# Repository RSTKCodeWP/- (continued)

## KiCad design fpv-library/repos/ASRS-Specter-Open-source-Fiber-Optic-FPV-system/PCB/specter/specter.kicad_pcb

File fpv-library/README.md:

# FPV Library

Automated mirror and catalog of FPV / drone open-source projects from GitHub.

## Is continuous sync realistic?

**Yes, with limits.**

| What works well | What needs care |
|-----------------|-----------------|
| Daily `discover` + `sync` via GitHub Actions | GitHub API rate limits (~5k req/hr authenticated) |
| Tracking upstream commit SHA per repo | Large repos (ardupilot, betaflight, firmware) take longer to clone — still synced |
| Owner expansion (other repos by same author) | Not every search hit is worth mirroring — scoring filters noise |
| Auto-commit when upstream changes | Licenses must be respected (GPL, etc.) |

This library keeps a **`catalog.json`** manifest: source repo, local path, last upstream commit, discovery method, relevance score.

## Layout

```
fpv-library/
  catalog.json          # manifest of all tracked projects
  STRUCTURE.md          # what each folder/file means (UA + EN)
  repos/                # auto-synced mirrors (discovered repos)
  ../OpenIPC/           # example: full git copies of a GitHub org
  manifests/            # release SHA256 manifests (Caddx firmware, ground config)
  ground-config/        # downloaded Caddx Ground Configuration binaries (gitignored)
  scripts/
    discover.py         # parse GitHub search + expand owners
    discover_themes.py  # multi-query themed discovery (GCS, fiber, WFB, …)
    sync.py             # full git mirror: clone, fetch, LFS, submodules
    discover_org.py     # register all repos from a GitHub org (e.g. OpenIPC)
    generate_repo_index.py  # write ../REPOS.md (full project list)
    register_legacy.py  # register hand-copied example folders at repo root
  THEMED.md             # curated highlights by category
  HOOKS.md              # auto-generated interesting / watch list
```

**Full project index (description, path, date, size):** [`../REPOS.md`](../REPOS.md)  
**Exhibition wiki (one card per folder on disk):** [`../wiki/Home.md`](../wiki/Home.md)  
**Daily mirror policy:** [`MIRROR.md`](MIRROR.md) · [`../docs/MIRROR_POLICY.md`](../docs/MIRROR_POLICY.md)  
**Repository layout:** [`../docs/STRUCTURE.md`](../docs/STRUCTURE.md) · [`STRUCTURE.md`](STRUCTURE.md)

## Usage

### Discover (GitHub search + owner crawl)

```bash
# Page 4 of Fpv search, expand each owner's other repos
python3 fpv-library/scripts/discover.py \
  --search Fpv \
  --page 4 \
  --min-score 2.0 \
  --expand-owners \
  --owner-limit 5

# Pages 1–5
python3 fpv-library/scripts/discover.py --search Fpv --pages 1-5 --expand-owners

# Themed batch: GCS, fiber, WFB, OpenIPC, DroneBridge, owner ecosystems
python3 fpv-library/scripts/discover_themes.py --pages 1-2 --min-score 2.5

# Full org library (e.g. all OpenIPC repos → OpenIPC/<repo>/)
python3 fpv-library/scripts/discover_org.py --org OpenIPC --verdict keep
python3 fpv-library/scripts/sync.py --owner OpenIPC --verdict keep
```

See [`THEMED.md`](THEMED.md) for curated project highlights.

### Daily mirror (update + backfill)

```bash
# Full daily cycle (same as CI)
python3 fpv-library/scripts/sync_daily.py

# Or manually:
python3 fpv-library/scripts/sync.py --all --verdict keep --update-only
python3 fpv-library/scripts/sync.py --all --verdict keep --new-only --max-per-run 25
```

### Sync upstream updates

```bash
python3 fpv-library/scripts/sync.py --all
python3 fpv-library/scripts/sync.py --source RotorHazard/RotorHazard
```

Each synced folder gets `.fpv-library.json` with upstream commit metadata.

### Register legacy examples

```bash
python3 fpv-library/scripts/register_legacy.py
```

## Automation

`.github/workflows/fpv-library-sync.yml` runs **daily** (06:00 UTC):

1. **Keyword discovery** — rotating batch from `keywords.txt`
2. **Themed discovery** — GCS / link / fiber queries + owner ecosystems
3. **Triage** — `keep` / `watch` / `skip`; write `HOOKS.md`
4. **Register** — root-level project folders → catalog
5. **Mirror** — `sync_daily.py`: update all existing + clone ~25 new `keep` repos
6. **Index** — regenerate root `REPOS.md`
7. **Commit** — push catalog + mirror updates

Manual run: Actions → **FPV Library Sync** → Run workflow (adjust `backfill_per_run`).

### Keyword discovery

```bash
# Today's rotating batch (12 keywords)
python3 fpv-library/scripts/discover_keywords.py --pages 1 --expand-owners

# All keywords (heavy — uses API quota)
python3 fpv-library/scripts/discover_keywords.py --no-rotate --pages 1-2 --expand-owners
```

Edit `keywords.txt` to add search terms.

### Blocklist

`blocklist.txt` — repos never added to catalog (Telegram bots, mail bots, games, etc.).

### Triage hooks

When a search hit looks like a "hook", triage assigns:

| Verdict | Meaning |
|---------|---------|
| `keep` | Useful — auto-synced |
| `watch` | Weak signal — listed in `HOOKS.md` for review |
| `skip` | Noise (coursework, dotfiles, unrelated) |

```bash
python3 fpv-library/scripts/triage_catalog.py --force   # re-classify all
cat fpv-library/HOOKS.md                                 # interesting + watch list
```

### Sync policies

```bash
python3 fpv-library/scripts/sync.py --all --verdict keep
```

## Relevance scoring

`scripts/fpv_lib/scoring.py` scores repos by keywords (fpv, betaflight, inav, osd, vtx, elrs, …), stars, and negative signals (shop sites, empty dumps). Default `--min-score 2.0` filters low-quality hits.

## Adding search queries

Edit discover invocations or extend the workflow to rotate queries:

- `Fpv`
- `betaflight`
- `inav drone`
- `openipc fpv`
- `expresslrs`

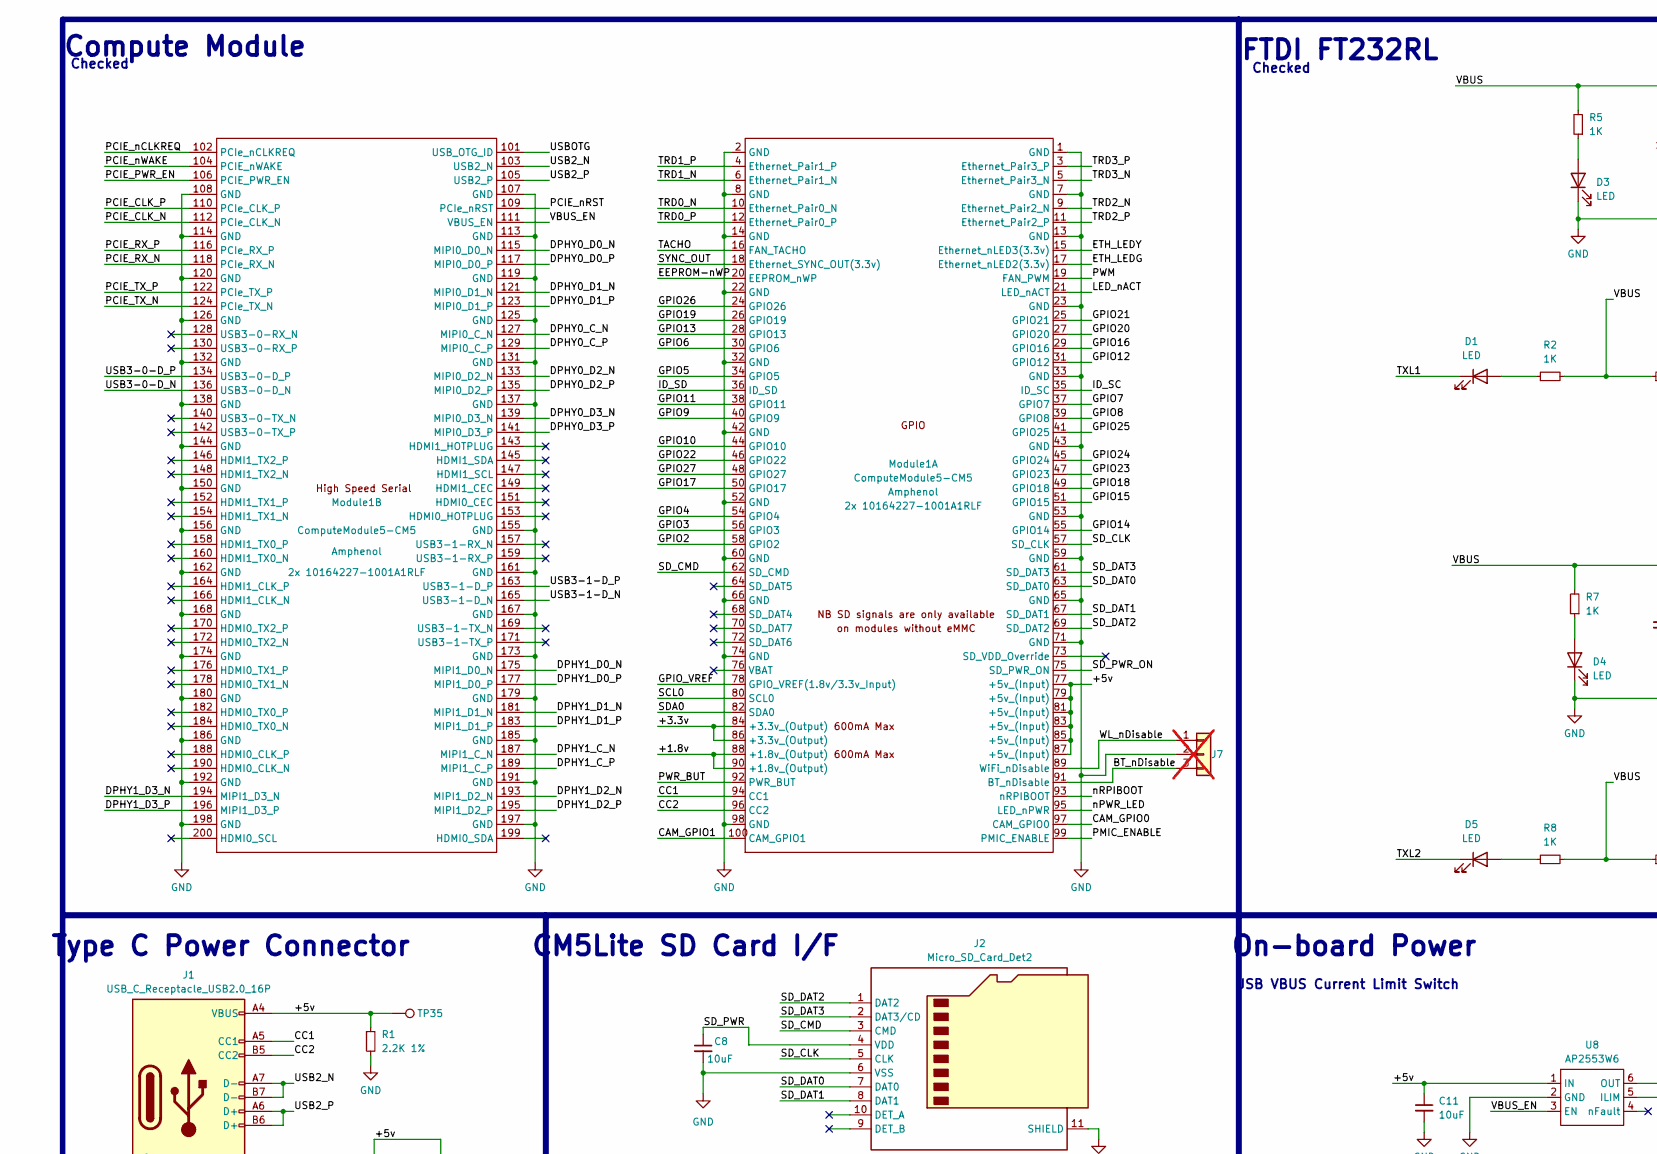
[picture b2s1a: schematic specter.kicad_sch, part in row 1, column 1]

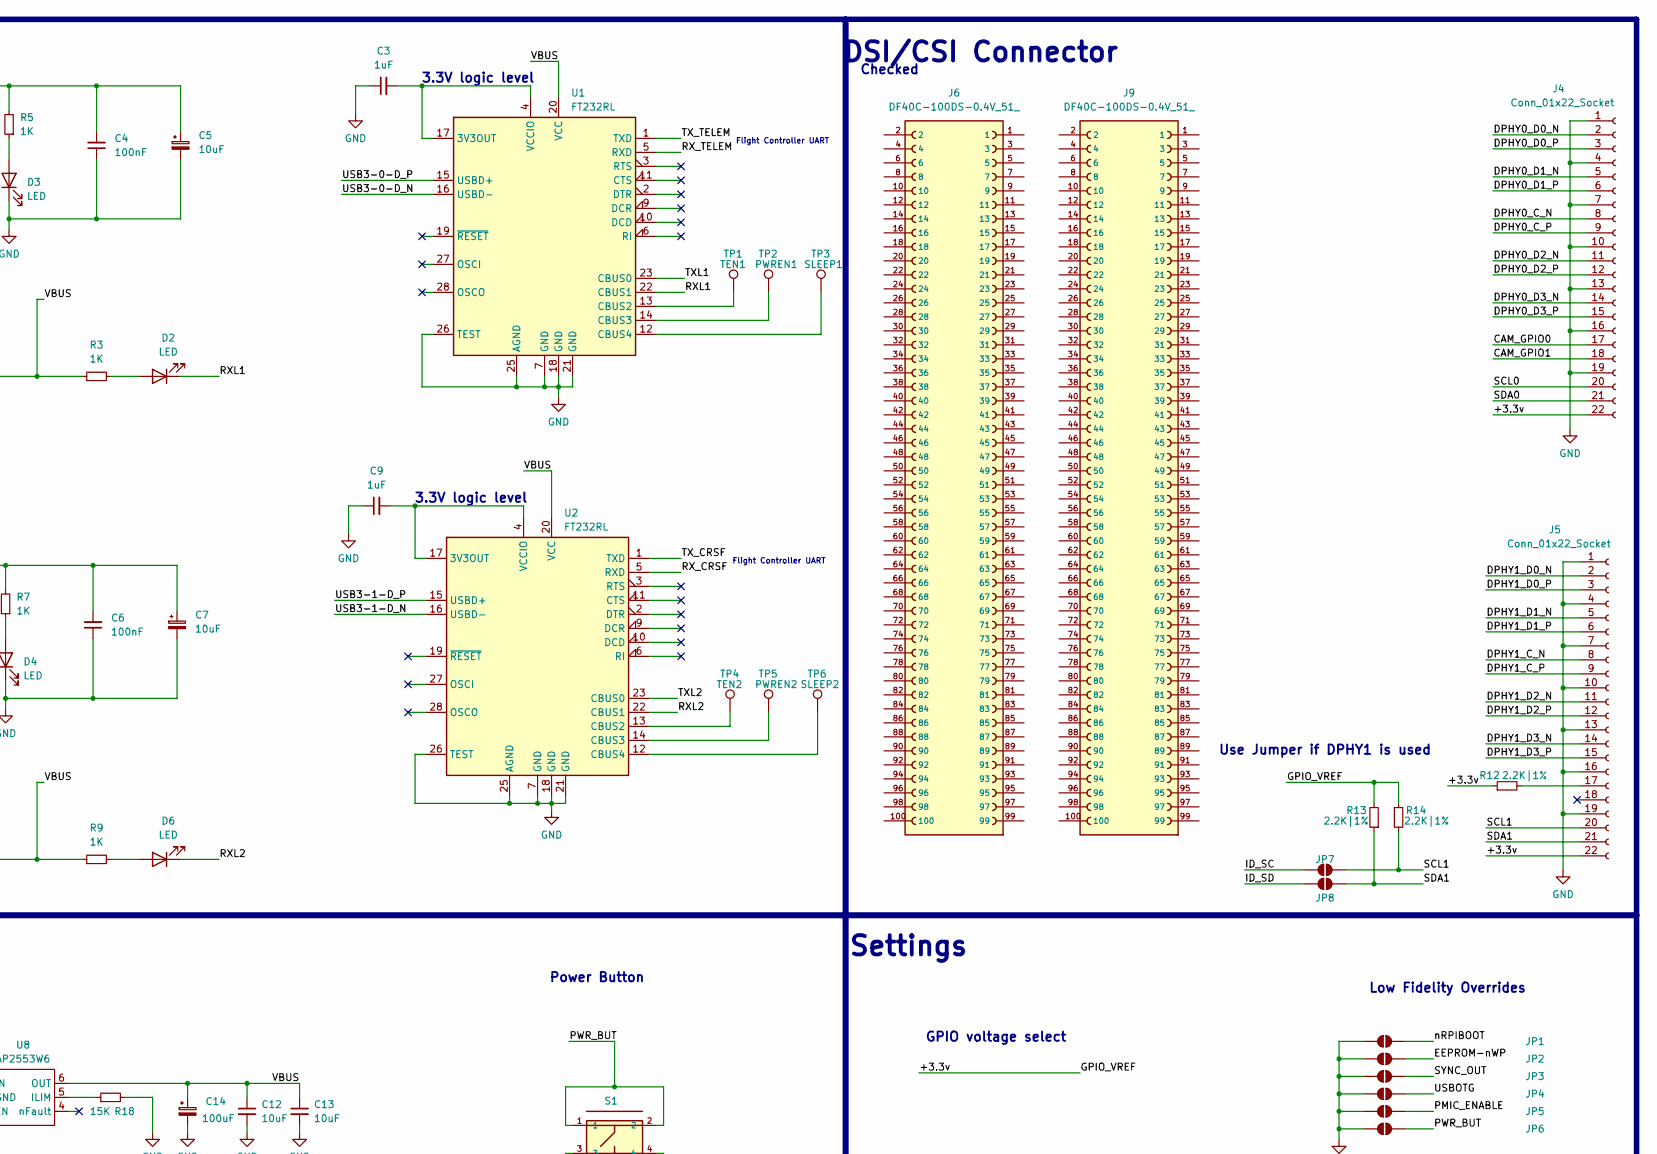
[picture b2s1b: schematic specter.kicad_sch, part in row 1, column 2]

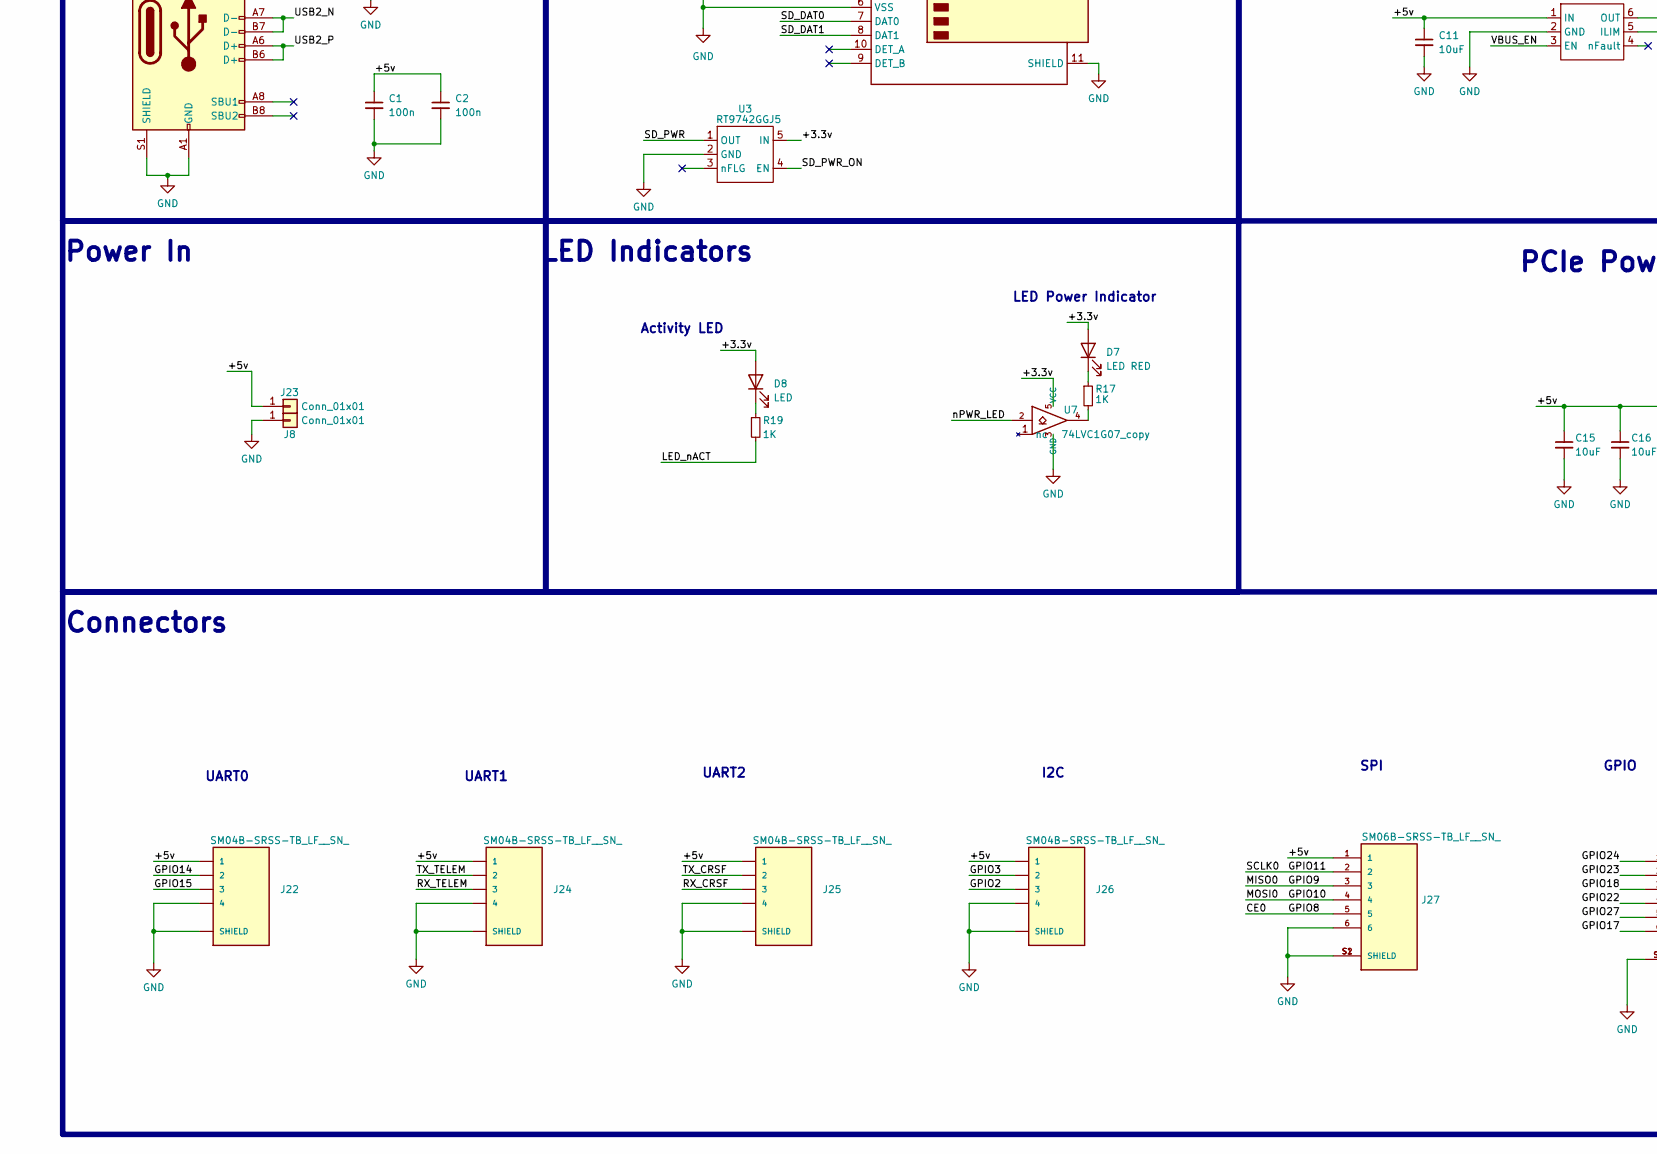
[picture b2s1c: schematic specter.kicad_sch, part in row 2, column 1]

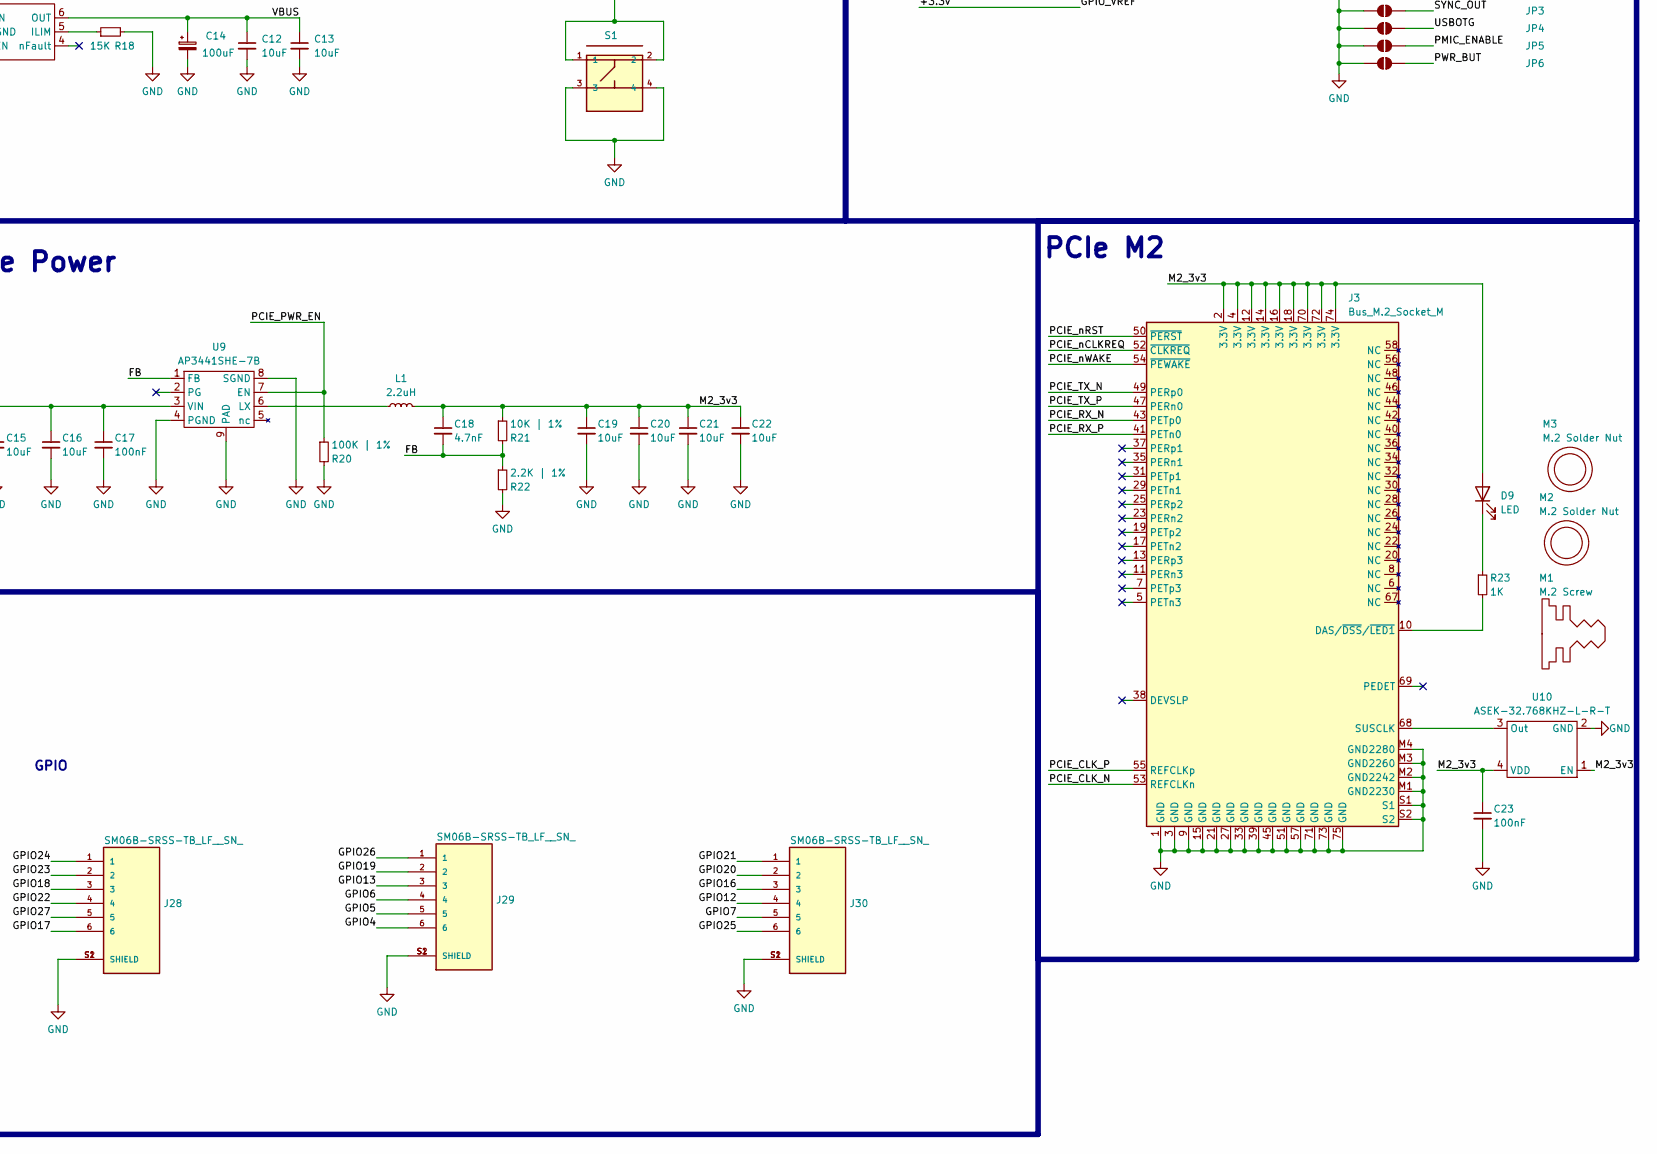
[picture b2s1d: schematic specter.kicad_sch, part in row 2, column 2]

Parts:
C1, C2: 100n; C_0402_1005Metric
C3, C9: 1uF; C_0805_2012Metric_Pad1.18x1.45mm_HandSolder
C4, C6: 100nF; C_0805_2012Metric_Pad1.18x1.45mm_HandSolder
C5, C7: 10uF; C_1206_3216Metric_Pad1.33x1.80mm_HandSolder
C8, C11, C12, C13, C15, C16, C19, C20, C21, C22: 10uF; C_0805_2012Metric
C14: 100uF; CP_EIA-7343-31_Kemet-D
C17, C23: 100nF; C_0402_1005Metric
C18: 4.7nF; C_0402_1005Metric
D1, D2, D3, D4, D5, D6, D9: LED; LED_0805_2012Metric_Pad1.15x1.40mm_HandSolder
D7: LED RED; LED_0603_1608Metric
D8: LED; LED_0603_1608Metric
J1: USB_C_Receptacle_USB2.0_16P; USB_C_Receptacle_GCT_USB4105-xx-A_16P_TopMnt_Horizontal
J2: Micro_SD_Card_Det2; SDCARD_MOLEX_503398-1892
J3: Bus_M.2_Socket_M; M.2 M Key socket
J4, J5: Conn_01x22_Socket; Hirose_FH12-22S-0.5SH_1x22-1MP_P0.50mm_Horizontal
J6, J9: DF40C-100DS-0.4V_51_; HIROSE_DF40C-100DS-0.4V_51_; PARTREV Oct.1.2023
J7: Conn_01x03; SolderJumper-3_P1.3mm_Open_RoundedPad1.0x1.5mm_NumberLabels; not fitted
J8, J23: Conn_01x01; TestPoint_THTPad_4.0x4.0mm_Drill2.0mm
J22, J24, J25, J26: SM04B-SRSS-TB_LF__SN_; JST_SM04B-SRSS-TB_LF__SN_
J27, J28, J29, J30: SM06B-SRSS-TB_LF__SN_; JST_SM06B-SRSS-TB_LF__SN_
JP1, JP2, JP3, JP4, JP5, JP6: SolderJumper_2_Open; SolderJumper-2_P1.3mm_Open_Pad1.0x1.5mm
JP7, JP8: SolderJumper_2_Open; SolderJumper-2_P1.3mm_Open_RoundedPad1.0x1.5mm
L1: 2.2uH; L_Bourns_SRP5030CC
M1: M.2 Screw
M2, M3: M.2 Solder Nut
Module1: ComputeModule5-CM5; Raspberry-Pi-5-Compute-Module
R1: 2.2K 1%; R_0402_1005Metric
R2, R3, R5, R7, R8, R9: 1K; R_0805_2012Metric_Pad1.20x1.40mm_HandSolder
R12, R13, R14: 2.2K|1%; R_0402_1005Metric
R17, R19, R23: 1K; R_0402_1005Metric
R18: 15K; R_0402_1005Metric
R20: 100K | 1%; R_0402_1005Metric
R21: 10K | 1%; R_0402_1005Metric
R22: 2.2K | 1%; R_0402_1005Metric
S1: SKQGAFE010; SW_SKQGAFE010; PART_REV B1
TP1: TEN1; TestPoint_Pad_D1.0mm
TP2: PWREN1; TestPoint_Pad_D1.0mm
TP3: SLEEP1; TestPoint_Pad_D1.0mm
TP4: TEN2; TestPoint_Pad_D1.0mm
TP5: PWREN2; TestPoint_Pad_D1.0mm
TP6: SLEEP2; TestPoint_Pad_D1.0mm
TP35: TestPoint; TestPoint_Pad_D1.0mm
U1, U2: FT232RL; SSOP-28_5.3x10.2mm_P0.65mm
U3: RT9742GGJ5; SOT-23-5
U7: 74LVC1G07_copy; SOT-353_SC-70-5
U8: AP2553W6; SOT-23-6
U9: AP3441SHE-7B; DFN-8-1EP_2x2mm_P0.5mm_EP1.05x1.75mm
U10: ASEK-32.768KHZ-L-R-T; Crystal_SMD_3225-4Pin_3.2x2.5mm

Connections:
/+1.8v: Module1.88 (+1.8v_(Output)), Module1.90 (+1.8v_(Output))
/+3.3v: D7.2 (A), D8.2 (A), J4.22, J5.22, Module1.78 (GPIO_VREF(1.8v/3.3v_Input)), Module1.84 (+3.3v_(Output)), Module1.86 (+3.3v_(Output)), R12.1, R13.2, R14.1, U3.5 (IN), U7.5 (VCC); also elsewhere on the board
/+5v: C1.1, C2.1, C11.1, C15.1, C16.1, C17.1, J1.A4 (VBUS), J1.A9 (VBUS), J1.B4 (VBUS), J1.B9 (VBUS), J22.1, J23.1, J24.1, J25.1, J26.1, J27.1, Module1.77 (+5v_(Input)), Module1.79 (+5v_(Input)), Module1.81 (+5v_(Input)), Module1.83 (+5v_(Input)), Module1.85 (+5v_(Input)), Module1.87 (+5v_(Input)), R1.1, TP35.1, U8.1 (IN), U9.3 (VIN)
/BT_nDisable: J7.3, Module1.91 (BT_nDisable)
/CAM_GPIO0: J4.17, Module1.97 (CAM_GPIO0)
/CAM_GPIO1: J4.18, Module1.100 (CAM_GPIO1)
/CC1: J1.A5 (CC1), Module1.94 (CC1)
/CC2: J1.B5 (CC2), Module1.96 (CC2)
/CE0: J27.5, Module1.39 (GPIO8)
/DPHY0_D0_N: J4.2, Module1.115 (MIPI0_D0_N)
/DPHY0_D0_P: J4.3, Module1.117 (MIPI0_D0_P)
/DPHY0_D1_N: J4.5, Module1.121 (MIPI0_D1_N)
/DPHY0_D1_P: J4.6, Module1.123 (MIPI0_D1_P)
/DPHY0_D2_N: J4.11, Module1.133 (MIPI0_D2_N)
/DPHY0_D2_P: J4.12, Module1.135 (MIPI0_D2_P)
/DPHY0_D3_N: J4.14, Module1.139 (MIPI0_D3_N)
/DPHY0_D3_P: J4.15, Module1.141 (MIPI0_D3_P)
/DPHY1_C_N: J5.8, Module1.187 (MIPI1_C_N)
/DPHY1_C_P: J5.9, Module1.189 (MIPI1_C_P)
/DPHY1_D0_N: J5.2, Module1.175 (MIPI1_D0_N)
/DPHY1_D0_P: J5.3, Module1.177 (MIPI1_D0_P)
/DPHY1_D1_N: J5.5, Module1.181 (MIPI1_D1_N)
/DPHY1_D1_P: J5.6, Module1.183 (MIPI1_D1_P)
/DPHY1_D2_N: J5.11, Module1.193 (MIPI1_D2_N)
/DPHY1_D2_P: J5.12, Module1.195 (MIPI1_D2_P)
/DPHY1_D3_N: J5.14, Module1.194 (MIPI1_D3_N)
/DPHY1_D3_P: J5.15, Module1.196 (MIPI1_D3_P)
/DPHY_C_N: J4.8, Module1.127 (MIPI0_C_N)
/DPHY_C_P: J4.9, Module1.129 (MIPI0_C_P)
/EEPROM-nWP: JP2.2 (B), Module1.20 (EEPROM_nWP)
/ETH_LEDG: Module1.17 (Ethernet_nLED2(3.3v))
/ETH_LEDY: Module1.15 (Ethernet_nLED3(3.3v))
/FB: C18.2, R21.2, R22.1, U9.1 (FB)
/GPIO2: J26.3, Module1.58 (GPIO2)
/GPIO3: J26.2, Module1.56 (GPIO3)
/GPIO4: J29.6, Module1.54 (GPIO4)
/GPIO5: J29.5, Module1.34 (GPIO5)
/GPIO6: J29.4, Module1.30 (GPIO6)
/GPIO7: J30.5, Module1.37 (GPIO7)
/GPIO9: J27.3, Module1.40 (GPIO9)
/GPIO10: J27.4, Module1.44 (GPIO10)
/GPIO11: J27.2, Module1.38 (GPIO11)
/GPIO12: J30.4, Module1.31 (GPIO12)
/GPIO13: J29.3, Module1.28 (GPIO13)
/GPIO14: J22.2, Module1.55 (GPIO14)
/GPIO15: J22.3, Module1.51 (GPIO15)
/GPIO16: J30.3, Module1.29 (GPIO16)
/GPIO17: J28.6, Module1.50 (GPIO17)
/GPIO18: J28.3, Module1.49 (GPIO18)
/GPIO19: J29.2, Module1.26 (GPIO19)
/GPIO20: J30.2, Module1.27 (GPIO20)
/GPIO21: J30.1, Module1.25 (GPIO21)
/GPIO22: J28.4, Module1.46 (GPIO22)
/GPIO23: J28.2, Module1.47 (GPIO23)
/GPIO24: J28.1, Module1.45 (GPIO24)
/GPIO25: J30.6, Module1.41 (GPIO25)
/GPIO26: J29.1, Module1.24 (GPIO26)
/GPIO27: J28.5, Module1.48 (GPIO27)
/ID_SC: JP7.1 (A), Module1.35 (ID_SC)
/ID_SD: JP8.1 (A), Module1.36 (ID_SD)
/LED_nACT: Module1.21 (LED_nACT), R19.2
/M2_3v3: C18.1, C19.1, C20.1, C21.1, C22.1, C23.1, D9.2 (A), J3.2 (3.3V), J3.4 (3.3V), J3.12 (3.3V), J3.14 (3.3V), J3.16 (3.3V), J3.18 (3.3V), J3.70 (3.3V), J3.72 (3.3V), J3.74 (3.3V), L1.2, R21.1, U10.1 (EN), U10.4 (VDD)
/PCIE_CLK_N: J3.53 (REFCLKn), Module1.112 (PCIe_CLK_N)
/PCIE_CLK_P: J3.55 (REFCLKp), Module1.110 (PCIe_CLK_P)
/PCIE_PWR_EN: Module1.106 (PCIE_PWR_EN), R20.1, U9.7 (EN)
/PCIE_RX_N: J3.43 (PETp0), Module1.118 (PCIe_RX_N)
/PCIE_RX_P: J3.41 (PETn0), Module1.116 (PCIe_RX_P)
/PCIE_TX_N: J3.49 (PERp0), Module1.124 (PCIe_TX_N)
/PCIE_TX_P: J3.47 (PERn0), Module1.122 (PCIe_TX_P)
/PCIE_nCLKREQ: J3.52 (~CLKREQ), Module1.102 (PCIe_nCLKREQ)
/PCIE_nRST: J3.50 (~PERST), Module1.109 (PCIe_nRST)
/PCIE_nWAKE: J3.54 (~PEWAKE), Module1.104 (PCIE_nWAKE)
/PMIC_ENABLE: JP5.2 (B), Module1.99 (PMIC_ENABLE)
/PWM: Module1.19 (FAN_PWM)
/PWR_BUT: JP6.2 (B), Module1.92 (PWR_BUT), S1.1, S1.2
/RXL1: D2.1 (K), U1.22 (CBUS1)
/RXL2: D6.1 (K), U2.22 (CBUS1)
/RX_CRSF: J25.3, U2.5 (RXD)
/RX_TELEM: J24.3, U1.5 (RXD)
/SCL0: J4.20, Module1.80 (SCL0)
/SCL1: J5.20, JP7.2 (B), R14.2
/SDA0: J4.21, Module1.82 (SDA0)
/SDA1: J5.21, JP8.2 (B), R13.1
/SD_CLK: J2.5 (CLK), Module1.57 (SD_CLK)
/SD_CMD: J2.3 (CMD), Module1.62 (SD_CMD)
/SD_DAT0: J2.7 (DAT0), Module1.63 (SD_DAT0)
/SD_DAT1: J2.8 (DAT1), Module1.67 (SD_DAT1)
/SD_DAT2: J2.1 (DAT2), Module1.69 (SD_DAT2)
/SD_DAT3: J2.2 (DAT3/CD), Module1.61 (SD_DAT3)
/SD_PWR: C8.1, J2.4 (VDD), U3.1 (OUT)
/SD_PWR_ON: Module1.75 (SD_PWR_ON), U3.4 (EN)
/SYNC_OUT: JP3.2 (B), Module1.18 (Ethernet_SYNC_OUT(3.3v))
/TACHO: Module1.16 (FAN_TACHO)
/TRD0_N: Module1.10 (Ethernet_Pair0_N)
/TRD0_P: Module1.12 (Ethernet_Pair0_P)
/TRD1_N: Module1.6 (Ethernet_Pair1_N)
/TRD1_P: Module1.4 (Ethernet_Pair1_P)
/TRD2_N: Module1.9 (Ethernet_Pair2_N)
/TRD2_P: Module1.11 (Ethernet_Pair2_P)
/TRD3_N: Module1.5 (Ethernet_Pair3_N)
/TRD3_P: Module1.3 (Ethernet_Pair3_P)
/TXL1: D1.1 (K), U1.23 (CBUS0)
/TXL2: D5.1 (K), U2.23 (CBUS0)
/TX_CRSF: J25.2, U2.1 (TXD)
/TX_TELEM: J24.2, U1.1 (TXD)
/USB2_N: J1.A7 (D-), J1.B7 (D-), Module1.103 (USB2_N)
/USB2_P: J1.A6 (D+), J1.B6 (D+), Module1.105 (USB2_P)
/USB3-0-D_N: Module1.136 (USB3-0-D_N), U1.16 (USBD-)
/USB3-0-D_P: Module1.134 (USB3-0-D_P), U1.15 (USBD+)
/USB3-1-D_N: Module1.165 (USB3-1-D_N), U2.16 (USBD-)
/USB3-1-D_P: Module1.163 (USB3-1-D_P), U2.15 (USBD+)
/USBOTG: JP4.2 (B), Module1.101 (USB_OTG_ID)
/VBUS: C4.2, C5.1, C6.2, C7.1, C12.1, C13.1, C14.1, R2.2, R3.1, R5.2, R7.2, R8.2, R9.1, U1.20 (VCC), U2.20 (VCC), U8.6 (OUT)
/VBUS_EN: Module1.111 (VBUS_EN), U8.3 (EN)
/WL_nDisable: J7.1, Module1.89 (WiFi_nDisable)
/nPWR_LED: Module1.95 (LED_nPWR), U7.2
/nRPIBOOT: JP1.2 (B), Module1.93 (nRPIBOOT)
GND: C1.2, C2.2, C3.1, C4.1, C5.2, C6.1, C7.2, C8.2, C9.1, C11.2, C12.2, C13.2, C14.2, C15.2, C16.2, C17.2, C19.2, C20.2, C21.2, C22.2, C23.2, D3.1 (K), D4.1 (K), J1.A1 (GND), J1.A12 (GND), J1.B1 (GND), J1.B12 (GND), J1.S1 (SHIELD), J2.6 (VSS), J2.11 (SHIELD), J3.1 (GND), J3.3 (GND), J3.9 (GND), J3.15 (GND), J3.21 (GND), J3.27 (GND), J3.33 (GND), J3.39 (GND), J3.45 (GND), J3.51 (GND), J3.57 (GND), J3.71 (GND), J3.73 (GND), J3.75 (GND), J3.M1 (GND2230), J3.M2 (GND2242), J3.M3 (GND2260), J3.M4 (GND2280), J3.S1, J3.S2, J4.1, J4.4, J4.7, J4.10, J4.13, J4.16, J4.19, J5.1, J5.4, J5.7, J5.10, J5.13, J5.16, J5.19, J7.2, J8.1, J22.4, J22.S1 (SHIELD), J22.S2 (SHIELD), J24.4, J24.S1 (SHIELD), J24.S2 (SHIELD), J25.4, J25.S1 (SHIELD), J25.S2 (SHIELD), J26.4, J26.S1 (SHIELD), J26.S2 (SHIELD), J27.6, J27.S1 (SHIELD), J27.S2 (SHIELD), J28.S1 (SHIELD), J28.S2 (SHIELD), J29.S1 (SHIELD), J29.S2 (SHIELD), J30.S1 (SHIELD), J30.S2 (SHIELD), JP1.1 (A), JP2.1 (A), JP3.1 (A), JP4.1 (A), JP5.1 (A), JP6.1 (A), Module1.1 (GND), Module1.2 (GND), Module1.7 (GND), Module1.8 (GND), Module1.13 (GND), Module1.14 (GND), Module1.22 (GND), Module1.23 (GND), Module1.32 (GND), Module1.33 (GND), Module1.42 (GND), Module1.43 (GND), Module1.52 (GND), Module1.53 (GND), Module1.59 (GND), Module1.60 (GND), Module1.65 (GND), Module1.66 (GND), Module1.71 (GND), Module1.74 (GND), Module1.98 (GND), Module1.107 (GND), Module1.108 (GND), Module1.113 (GND), Module1.114 (GND), Module1.119 (GND), Module1.120 (GND), Module1.125 (GND), Module1.126 (GND), Module1.131 (GND), Module1.132 (GND), Module1.137 (GND), Module1.138 (GND), Module1.144 (GND), Module1.150 (GND), Module1.155 (GND), Module1.156 (GND), Module1.161 (GND), Module1.162 (GND), Module1.167 (GND), Module1.168 (GND), Module1.173 (GND), Module1.174 (GND), Module1.179 (GND), Module1.180 (GND), Module1.185 (GND), Module1.186 (GND), Module1.191 (GND), Module1.192 (GND), Module1.197 (GND), Module1.198 (GND), R1.2, R18.2, R20.2, R22.2, S1.3, S1.4, U1.7 (GND), U1.18 (GND), U1.21 (GND), U1.25 (AGND), U1.26 (TEST), U2.7 (GND), U2.18 (GND), U2.21 (GND), U2.25 (AGND), U2.26 (TEST), U3.2 (GND), U7.3 (GND), U8.2 (GND), U9.4 (PGND), U9.8 (SGND), U9.9 (PAD), U10.2 (GND)
unnamed: D1.2 (A), R2.1
unnamed: D2.2 (A), R3.2
unnamed: D3.2 (A), R5.1
unnamed: D4.2 (A), R7.1
unnamed: D5.2 (A), R8.1
unnamed: D6.2 (A), R9.2
unnamed: D7.1 (K), R17.1
unnamed: D8.1 (K), R19.1
unnamed: D9.1 (K), R23.1
unnamed: J3.10 (DAS/~DSS/~LED1), R23.2
unnamed: J3.68 (SUSCLK), U10.3 (Out)
unnamed: J5.17, R12.2
unnamed: R17.2, U7.4
unnamed: C3.2, U1.4 (VCCIO), U1.17 (3V3OUT)
unnamed: TP1.1, U1.13 (CBUS2)
unnamed: TP2.1, U1.14 (CBUS3)
unnamed: TP3.1, U1.12 (CBUS4)
unnamed: C9.2, U2.4 (VCCIO), U2.17 (3V3OUT)
unnamed: TP4.1, U2.13 (CBUS2)
unnamed: TP5.1, U2.14 (CBUS3)
unnamed: TP6.1, U2.12 (CBUS4)
unnamed: R18.1, U8.5 (ILIM)
unnamed: L1.1, U9.6 (LX)

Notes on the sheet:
Checked
3.3V logic level
Low Fidelity Overrides
PCIe M2
PCIe Power
SPI
UART2
Activity LED
UART0
GPIO
LED Indicators
Type C Power Connector
I2C
Flight Controller UART
GPIO voltage select
UART1
Connectors
Settings
FTDI FT232RL
Use Jumper if DPHY1 is used
CM5Lite SD Card I/F
Power Button
LED Power Indicator
Compute Module
Power In
On-board Power
USB VBUS Current Limit Switch
DSI/CSI Connector

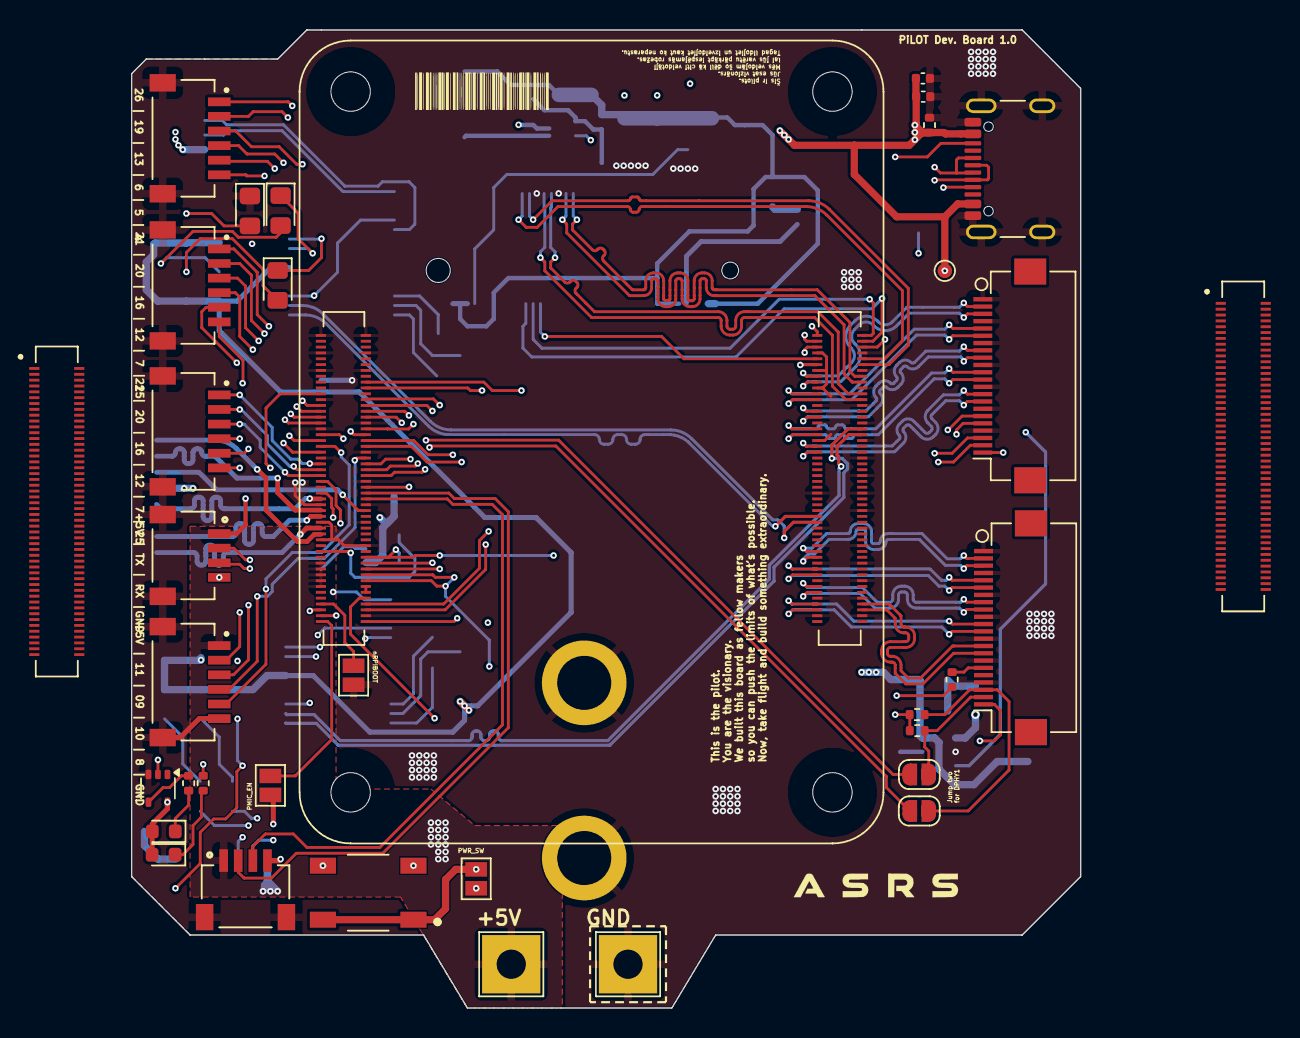
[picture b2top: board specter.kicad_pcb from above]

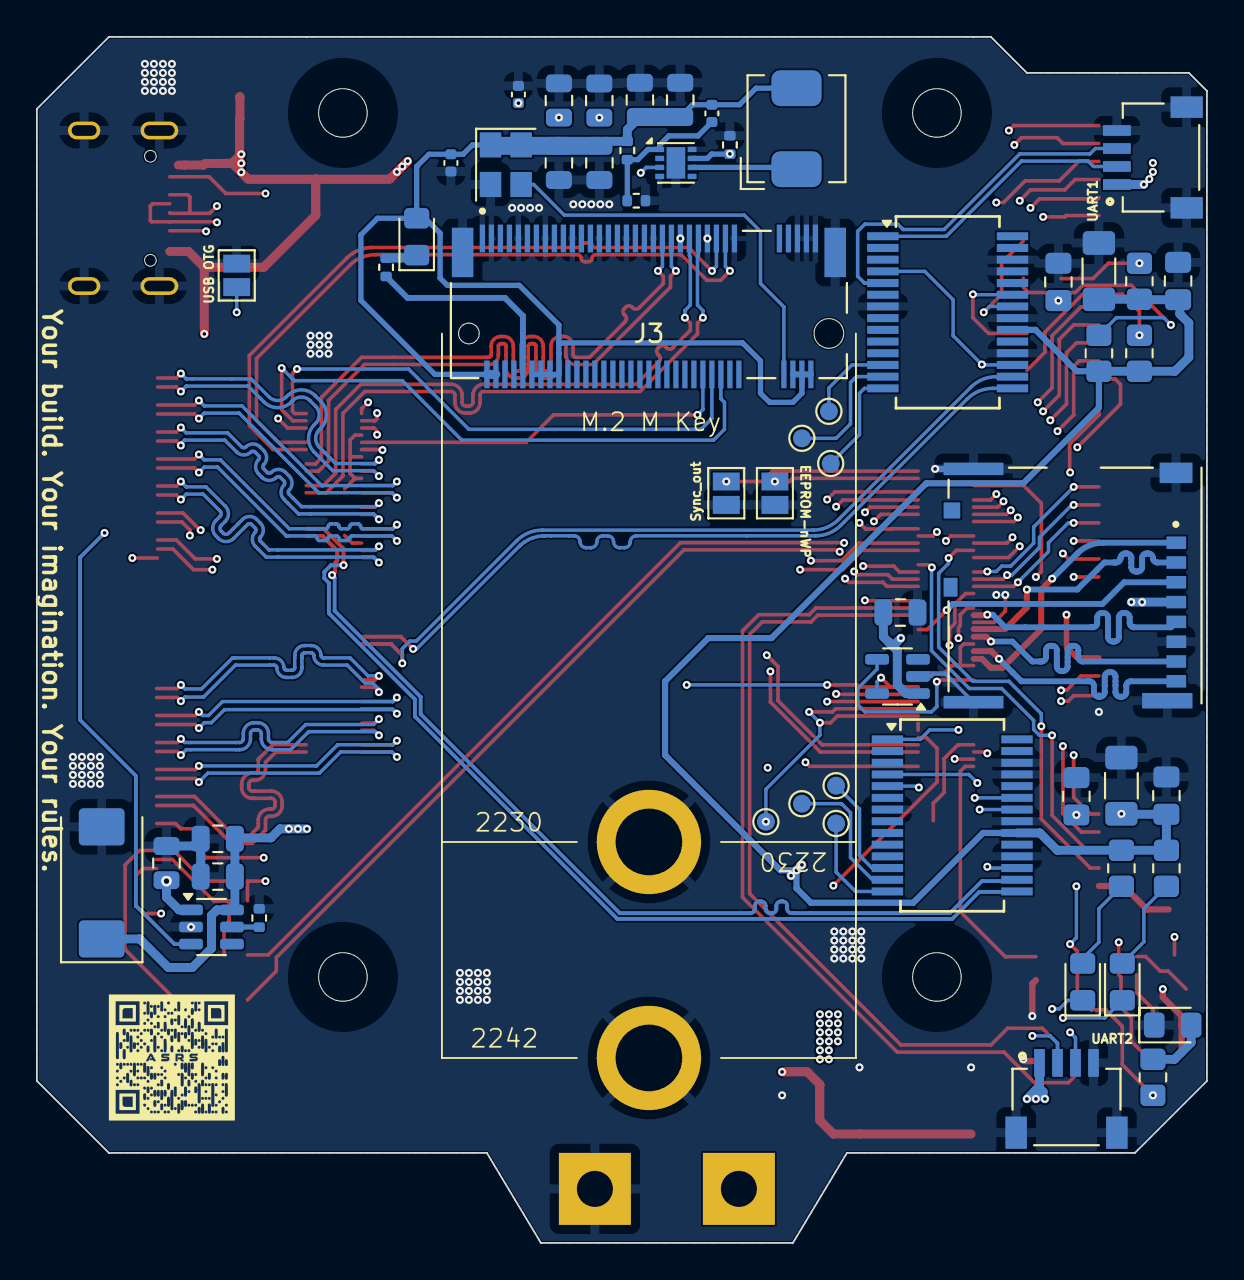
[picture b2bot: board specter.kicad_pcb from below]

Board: 4 copper layers, 65.0 x 67.0 mm, 91 parts (56 on the bottom side), 127 nets.

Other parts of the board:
TP33: TestPoint; TestPoint_Pad_D1.0mm

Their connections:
/+3.3v: TP33.1; also elsewhere on the board

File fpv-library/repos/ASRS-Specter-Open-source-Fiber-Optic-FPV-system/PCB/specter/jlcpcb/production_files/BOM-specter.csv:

Comment,Designator,Footprint,LCSC,Quantity
1K,"R17,R19,R23",R_0402_1005Metric,C11702,3
100uF,C14,CP_EIA-7343-31_Kemet-D,C122321,1
10uF,"C5,C7",C_1206_3216Metric_Pad1.33x1.80mm_HandSolder,C13585,2
Bus_M.2_Socket_M,J3,M.2 M Key socket,C1509730,1
100n,"C1,C17,C2,C23",C_0402_1005Metric,C1525,4
4.7nF,C18,C_0402_1005Metric,C1538,1
10uF,"C11,C12,C13,C15,C16,C19,C20,C21,C22,C8",C_0805_2012Metric,C15850,10
SM04B-SRSS-TB_LF__SN_,"J22,J24,J25,J26",JST_SM04B-SRSS-TB_LF__SN_,C160404,4
1K,"R2,R3,R5,R7,R8,R9",R_0805_2012Metric_Pad1.20x1.40mm_HandSolder,C17513,6
SKQGAFE010,S1,SW_SKQGAFE010,C202424,1
AP3441SHE-7B,U9,DFN-8-1EP_2x2mm_P0.5mm_EP1.05x1.75mm,C2070918,1
AP2553W6,U8,SOT-23-6,C212302,1
2.2uH,L1,L_Bourns_SRP5030CC,C22404330,1
LED RED,"D7,D8",LED_0603_1608Metric,C2290,2
LED,"D1,D2,D5,D6,D9",LED_0805_2012Metric_Pad1.15x1.40mm_HandSolder,C2297,5
SM06B-SRSS-TB_LF__SN_,"J27,J28,J29,J30",JST_SM06B-SRSS-TB_LF__SN_,C239524,4
RT9742GGJ5,U3,SOT-23-5,C250547,1
100K | 1%,R20,R_0402_1005Metric,C25741,1
10K | 1%,R21,R_0402_1005Metric,C25744,1
15K,R18,R_0402_1005Metric,C25756,1
2.2K 1%,"R1,R12,R13,R14,R22",R_0402_1005Metric,C25879,5
ASEK-32.768KHZ-L-R-T,U10,Crystal_SMD_3225-4Pin_3.2x2.5mm,C2650753,1
1uF,"C3,C9",C_0805_2012Metric_Pad1.18x1.45mm_HandSolder,C28323,2
LED,"D3,D4",LED_0805_2012Metric_Pad1.15x1.40mm_HandSolder,C34499,2
Micro_SD_Card_Det2,J2,SDCARD_MOLEX_503398-1892,C428492,1
100nF,"C4,C6",C_0805_2012Metric_Pad1.18x1.45mm_HandSolder,C49678,2
74LVC1G07_copy,U7,SOT-353_SC-70-5,C5138996,1
USB_C_Receptacle_USB2.0_16P,J1,USB_C_Receptacle_GCT_USB4105-xx-A_16P_TopMnt_Horizontal,C5187472,1
DF40C-100DS-0.4V_51_,"J6,J9",HIROSE_DF40C-100DS-0.4V_51_,C597931,2
Conn_01x22_Socket,"J4,J5",Hirose_FH12-22S-0.5SH_1x22-1MP_P0.50mm_Horizontal,C597981,2
FT232RL,"U1,U2",SSOP-28_5.3x10.2mm_P0.65mm,C8690,2

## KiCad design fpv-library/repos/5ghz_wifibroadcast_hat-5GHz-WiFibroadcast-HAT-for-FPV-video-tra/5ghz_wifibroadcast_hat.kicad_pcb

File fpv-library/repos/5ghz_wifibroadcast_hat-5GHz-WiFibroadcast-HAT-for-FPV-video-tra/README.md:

# 5GHz WiFi Broadcast HAT

A KiCad hardware design for a compact 5GHz WiFi Broadcast HAT.

It's based on RTL8812EU chipset inside BL-M8812EU2 module on the HAT.

Driver: [github.com/libc0607/rtl88x2eu-20230815](https://github.com/libc0607/rtl88x2eu-20230815)

Officially supported frequency: 5.15~5.85GHz.

**WARNING**: Use heatsink with fan like this one: [aliexpress.com/item/4000297043992.html](https://www.aliexpress.com/item/4000297043992.html).

**WARNING**: Connect antennas before usage.

Older version was bigger, this one was made more compact:

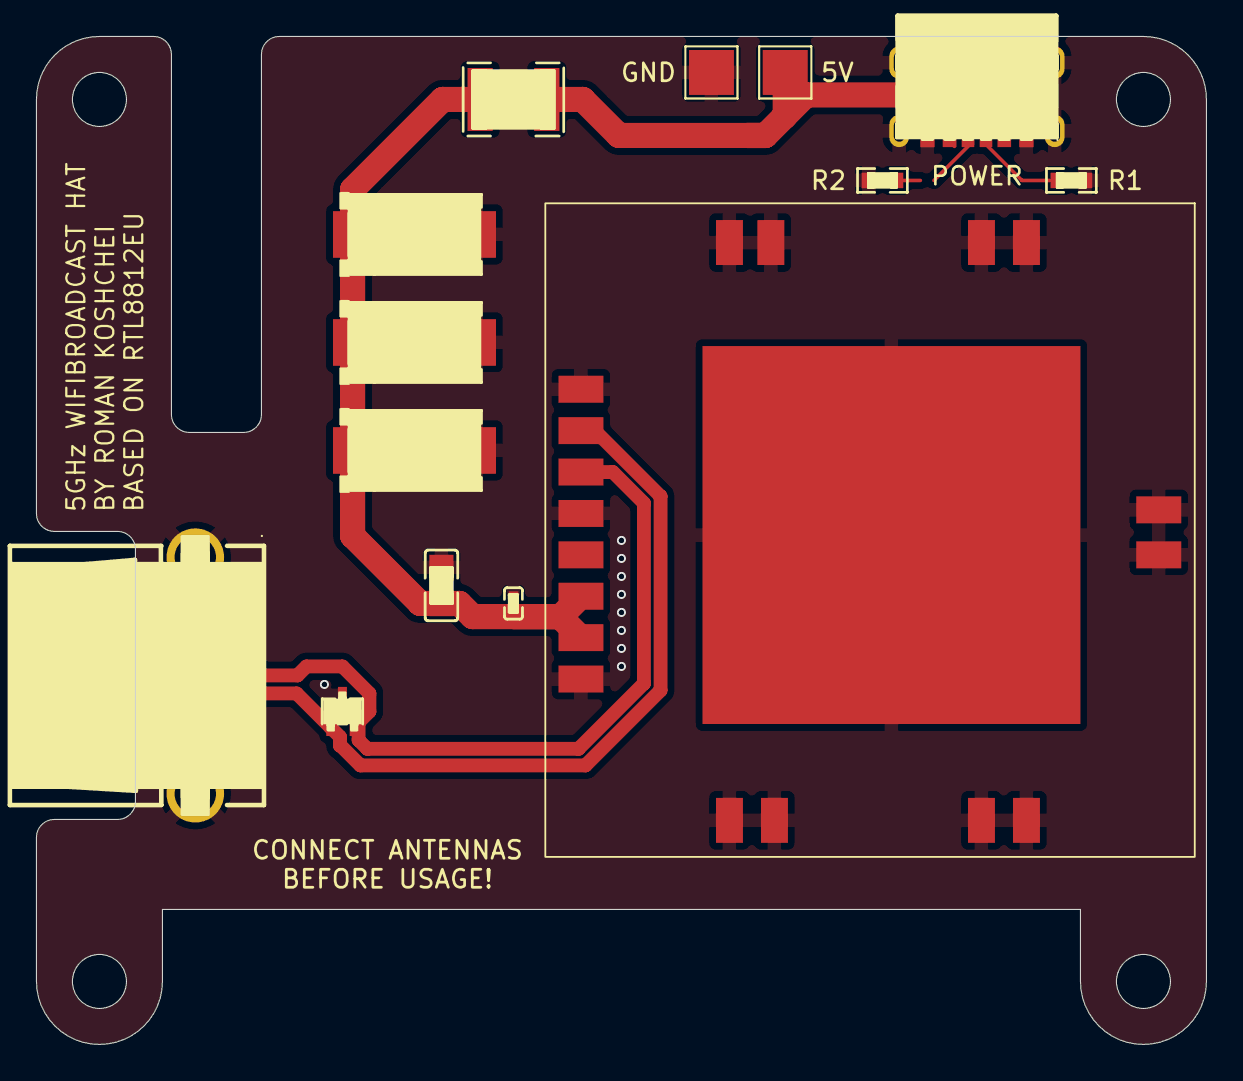
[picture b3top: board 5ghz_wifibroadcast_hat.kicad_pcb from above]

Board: 2 copper layers, 65.0 x 56.0 mm, 14 parts (0 on the bottom side), 7 nets.

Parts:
5V: Conn_01x01_Pin; TestPoint_Pad_2.5x2.5mm
BL1: BL-M8812EU2
C1: 0.1 µF; C0402
C2: 10 µF; C0805
C3, C4, C5: 10TPB220M; CAP-SMD_L7.3-W4.3-FD
DATA1: AF_90°_WJDG; USB-A-TH_AF-WJDG
F1: 1812L300/24GR; F1812
GND: Conn_01x01_Pin; TestPoint_Pad_2.5x2.5mm
POWER: TYPE-C-31-M-17; USB-C-SMD_10P-P1.00-L6.8-W8.9
R1, R2: 0603WAF5101T5E; R0603
U1: TPD2E2U06DCKR-TP; SOT-323-3_L2.0-W1.3-P1.30-LS2.1-BR

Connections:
/D+: BL1.2 (USB2.0+DP), DATA1.3 (D+), U1.1 (IO1)
/D-: BL1.3 (USB2.0-DM), DATA1.2 (D-), U1.2 (IO2)
GND: BL1.1 (GND), BL1.4 (GND), BL1.8 (GND), BL1.9 (GND), BL1.10 (GND), BL1.11 (GND), BL1.12 (GND), BL1.13 (GND), BL1.14 (GND), BL1.15 (GND), BL1.16 (GND), BL1.17 (GND), BL1.18 (GND), BL1.19 (GND), C1.2, C2.2, C3.2, C4.2, C5.2, DATA1.4 (GND), DATA1.5 (SHLD), GND.1 (Pin_1_1), POWER.0, POWER.1 (B12), POWER.6 (A12), R1.2, R2.2, U1.3 (GND)
unnamed: 5V.1 (Pin_1_1), F1.1, POWER.2 (B9), POWER.5 (A9)
unnamed: POWER.3 (A5), R1.1
unnamed: POWER.4 (B5), R2.1
VCC: BL1.6 (VDD5.0), BL1.7 (VDD5.0), C1.1, C2.1, C3.1, C4.1, C5.1, F1.2
